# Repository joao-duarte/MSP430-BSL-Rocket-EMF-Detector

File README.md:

# MSP430-BSL-Rocket-EMF-Detector
EMF Detector with an MSP430 BSL Rocket
http://thefragmentationparadox.blogspot.pt/2015/04/msp430-bsl-rocket-emf-detector.html

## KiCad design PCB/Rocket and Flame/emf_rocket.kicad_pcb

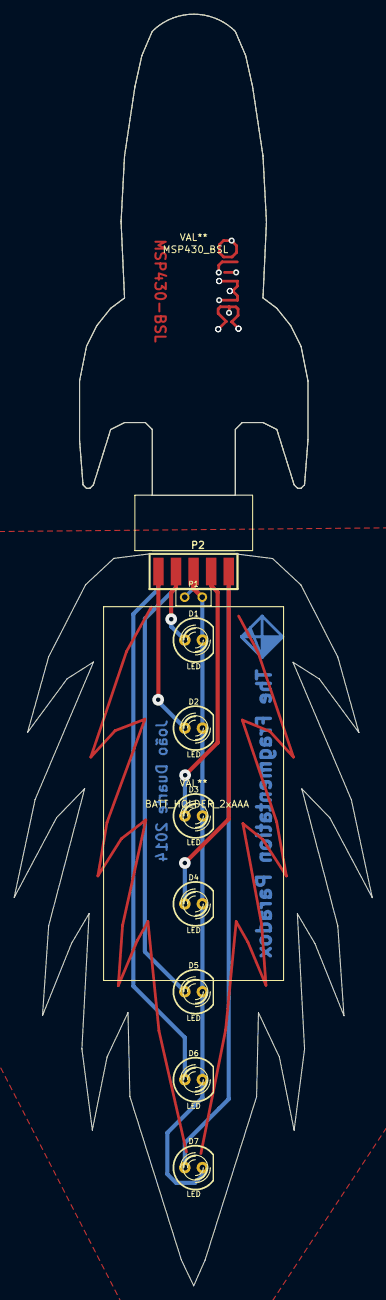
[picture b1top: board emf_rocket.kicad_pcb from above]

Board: 8 copper layers, 51.7 x 105.7 mm, 11 parts (0 on the bottom side), 9 nets.

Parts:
BATT_HOLDER_2xAAA: VAL**; BATT_HOLDER_2xAAA
D1, D2, D3, D4, D5, D6, D7: LED; LED-5MM
MSP430_BSL: VAL**; MSP430_BSL
P1: CONN_2; PIN_ARRAY_2X1
P2: CONN_10; PIN_ARRAY_5x2_SMD

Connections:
+3.3V: P1.1, P2.6
/P4_0: D4.1, P2.9
/P4_3: D7.1, P2.10
/P4_4: D1.1, P2.3
/P4_5: D2.1, P2.1
/PJ_1: D5.1, P2.4
/PJ_2: D3.1, P2.7
/PJ_3: D6.1, P2.2
GND: D1.2, D2.2, D3.2, D4.2, D5.2, D6.2, D7.2, P1.2, P2.5

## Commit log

2015-04-20 Ready for github!
2015-04-20 Correct indentation.
